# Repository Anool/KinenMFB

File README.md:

KinenMFB
========

Kinen Motherboard , Arduino based, with Raspberry-Pi interface

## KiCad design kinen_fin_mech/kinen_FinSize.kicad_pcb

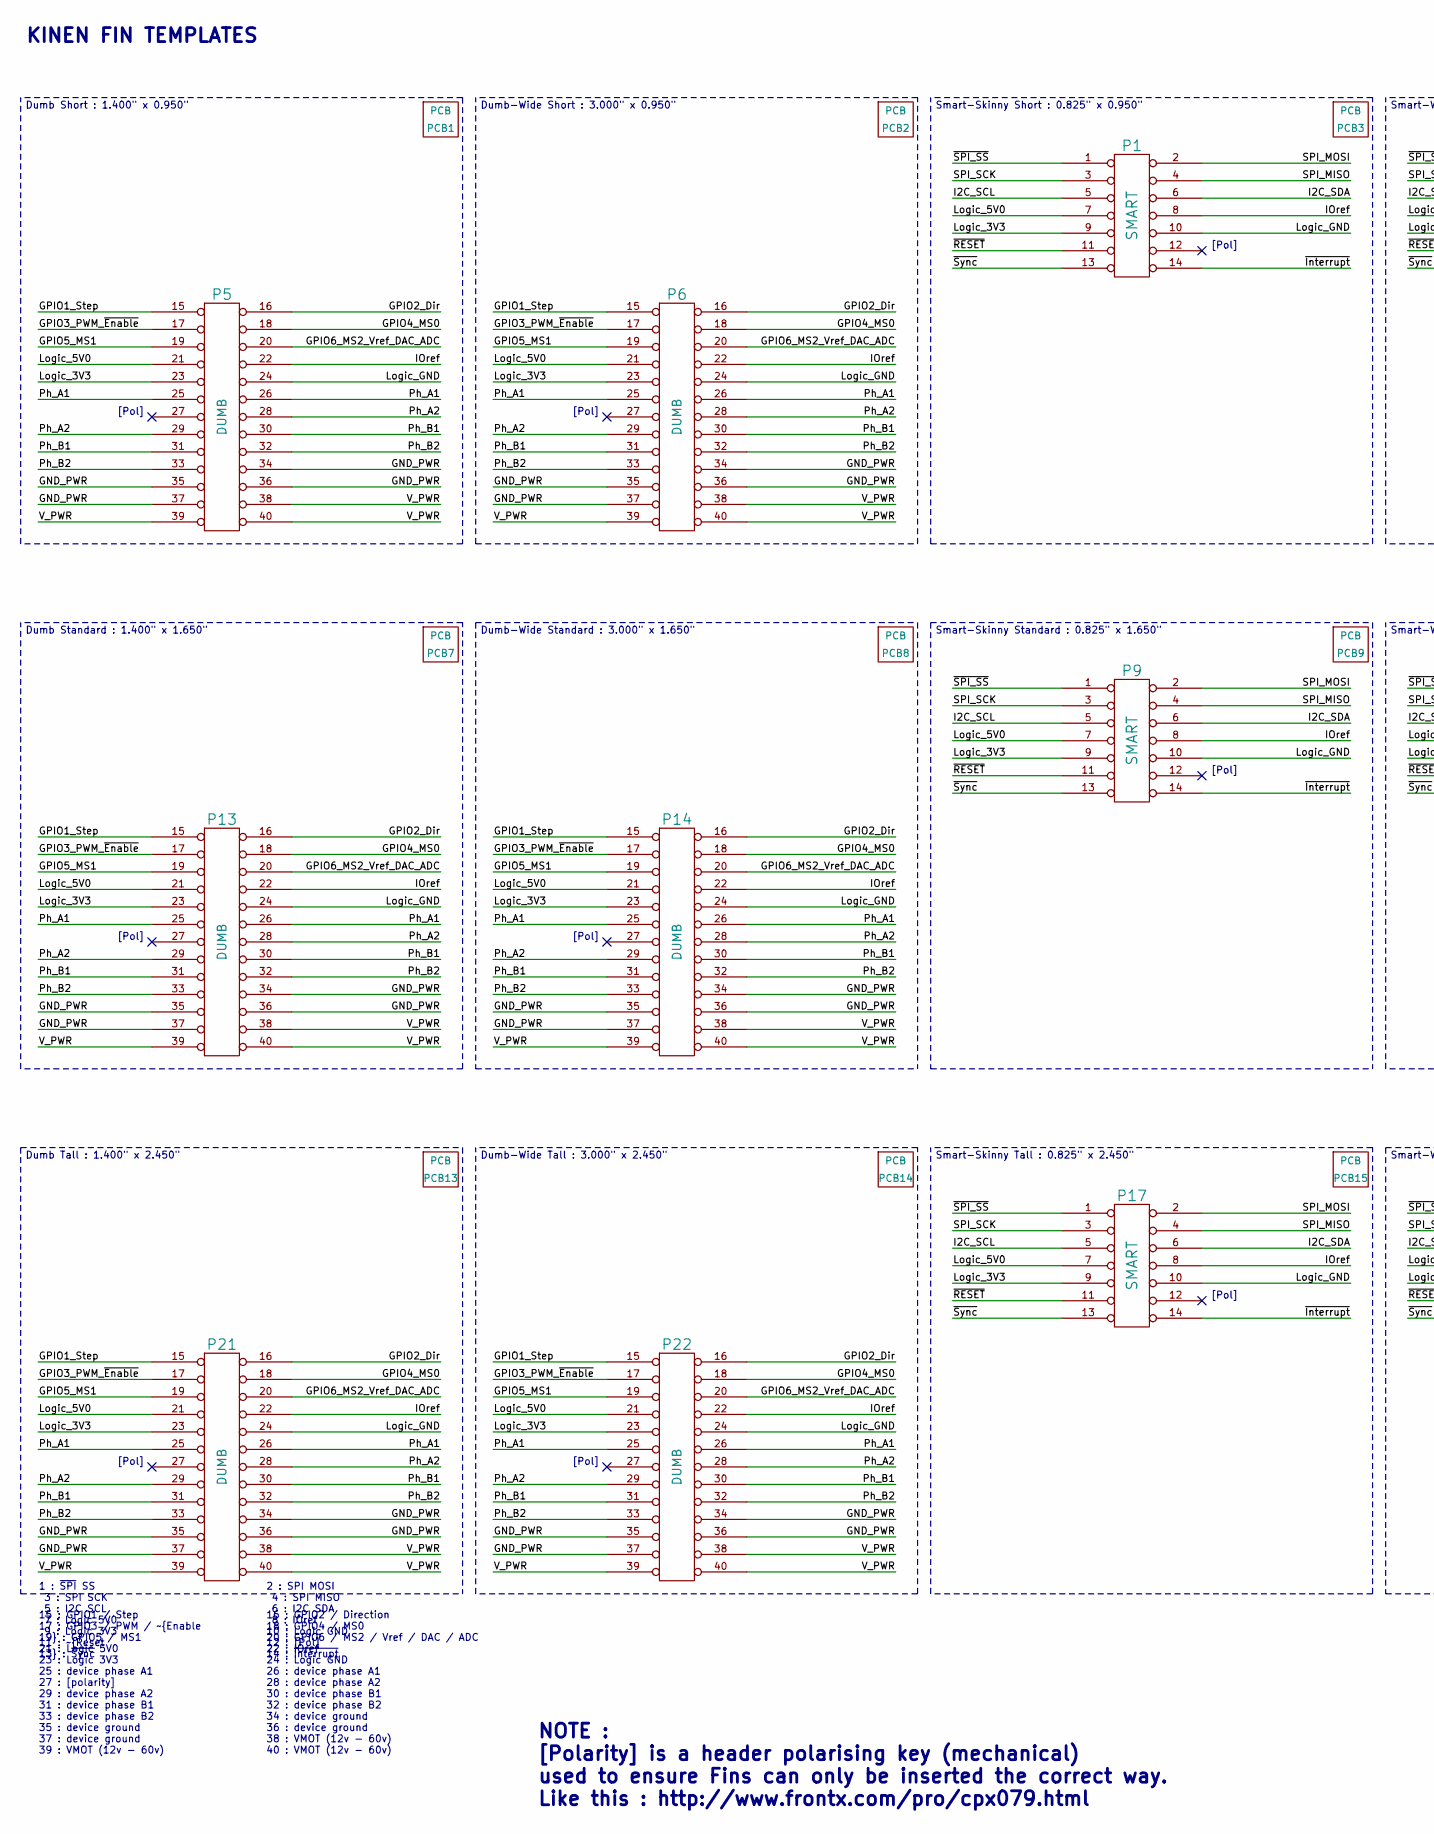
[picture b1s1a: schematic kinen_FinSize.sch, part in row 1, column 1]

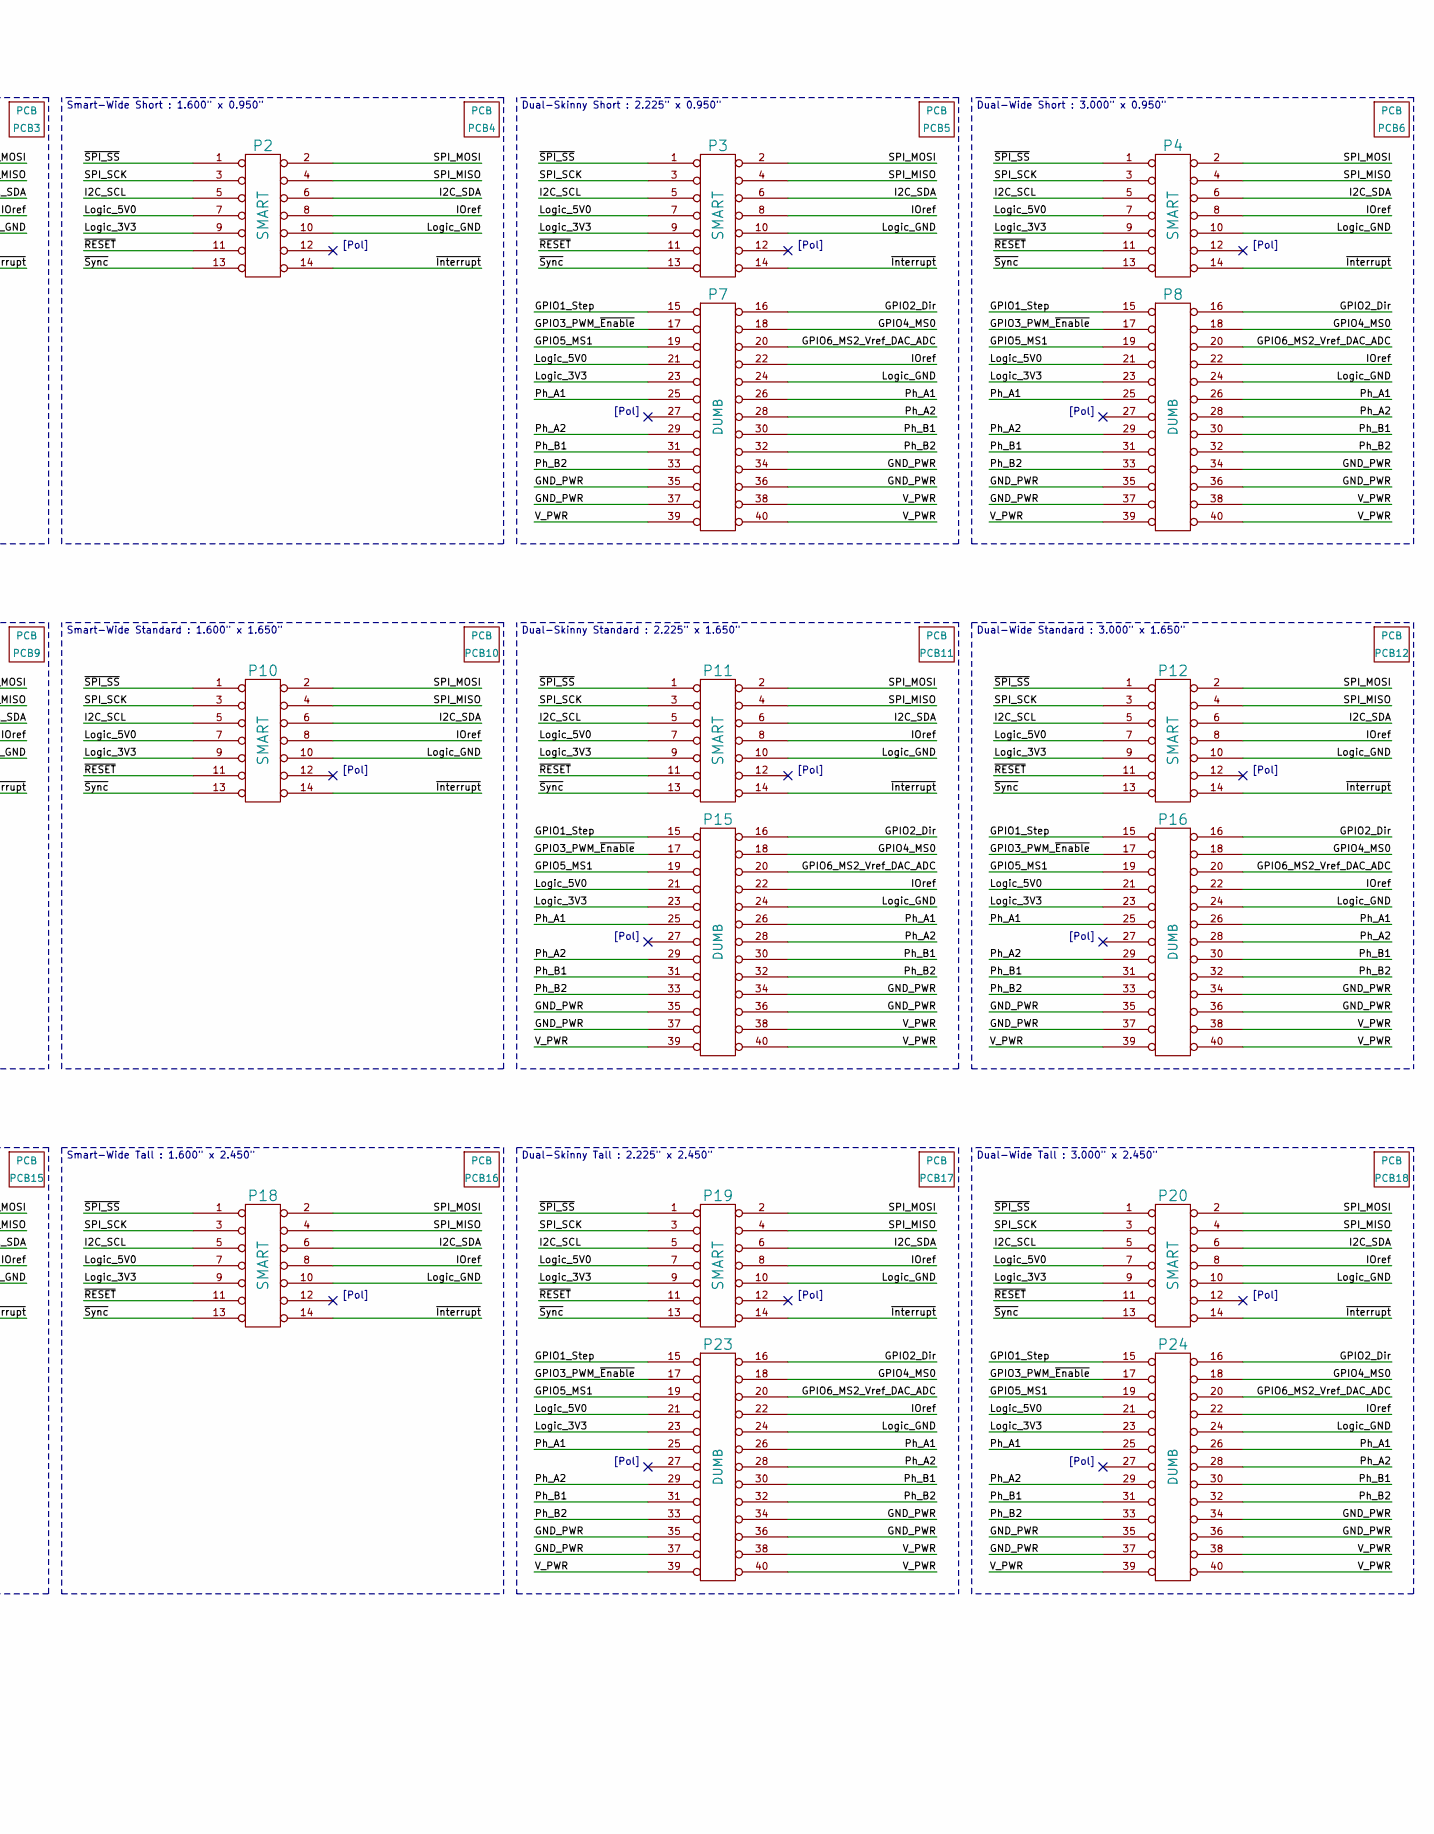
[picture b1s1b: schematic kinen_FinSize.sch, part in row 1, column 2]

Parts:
P1, P2, P3, P4, P9, P10, P11, P12, P17, P18, P19, P20: SMART; PinArray7x2/90
P5, P6, P7, P8, P13, P14, P15, P16, P21, P22, P23, P24: DUMB; PinArray13x2/90
PCB1, PCB2, PCB3, PCB4, PCB5, PCB6, PCB7, PCB8, PCB9, PCB10, PCB11, PCB12, PCB13, PCB14, PCB15, PCB16, PCB17, PCB18: PCB

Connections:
/GND_PWR: P5.34 (P20), P5.35 (P21), P5.36 (P22), P5.37 (P23), P6.34 (P20), P6.35 (P21), P6.36 (P22), P6.37 (P23), P7.34 (P20), P7.35 (P21), P7.36 (P22), P7.37 (P23), P8.34 (P20), P8.35 (P21), P8.36 (P22), P8.37 (P23), P13.34 (P20), P13.35 (P21), P13.36 (P22), P13.37 (P23), P14.34 (P20), P14.35 (P21), P14.36 (P22), P14.37 (P23), P15.34 (P20), P15.35 (P21), P15.36 (P22), P15.37 (P23), P16.34 (P20), P16.35 (P21), P16.36 (P22), P16.37 (P23), P21.34 (P20), P21.35 (P21), P21.36 (P22), P21.37 (P23), P22.34 (P20), P22.35 (P21), P22.36 (P22), P22.37 (P23), P23.34 (P20), P23.35 (P21), P23.36 (P22), P23.37 (P23), P24.34 (P20), P24.35 (P21), P24.36 (P22), P24.37 (P23)
/GPIO1_Step: P5.15 (P1), P6.15 (P1), P7.15 (P1), P8.15 (P1), P13.15 (P1), P14.15 (P1), P15.15 (P1), P16.15 (P1), P21.15 (P1), P22.15 (P1), P23.15 (P1), P24.15 (P1)
/GPIO2_Dir: P5.16 (P2), P6.16 (P2), P7.16 (P2), P8.16 (P2), P13.16 (P2), P14.16 (P2), P15.16 (P2), P16.16 (P2), P21.16 (P2), P22.16 (P2), P23.16 (P2), P24.16 (P2)
/GPIO3_PWM_~Enable: P5.17 (P3), P6.17 (P3), P7.17 (P3), P8.17 (P3), P13.17 (P3), P14.17 (P3), P15.17 (P3), P16.17 (P3), P21.17 (P3), P22.17 (P3), P23.17 (P3), P24.17 (P3)
/GPIO4_MS0: P5.18 (P4), P6.18 (P4), P7.18 (P4), P8.18 (P4), P13.18 (P4), P14.18 (P4), P15.18 (P4), P16.18 (P4), P21.18 (P4), P22.18 (P4), P23.18 (P4), P24.18 (P4)
/GPIO5_MS1: P5.19 (P5), P6.19 (P5), P7.19 (P5), P8.19 (P5), P13.19 (P5), P14.19 (P5), P15.19 (P5), P16.19 (P5), P21.19 (P5), P22.19 (P5), P23.19 (P5), P24.19 (P5)
/GPIO6_MS2_Vref_DAC_ADC: P5.20 (P6), P6.20 (P6), P7.20 (P6), P8.20 (P6), P13.20 (P6), P14.20 (P6), P15.20 (P6), P16.20 (P6), P21.20 (P6), P22.20 (P6), P23.20 (P6), P24.20 (P6)
/I2C_SCL: P1.5, P2.5, P3.5, P4.5, P9.5, P10.5, P11.5, P12.5, P17.5, P18.5, P19.5, P20.5
/I2C_SDA: P1.6, P2.6, P3.6, P4.6, P9.6, P10.6, P11.6, P12.6, P17.6, P18.6, P19.6, P20.6
/IOref: P1.8, P2.8, P3.8, P4.8, P5.22 (P8), P6.22 (P8), P7.22 (P8), P8.22 (P8), P9.8, P10.8, P11.8, P12.8, P13.22 (P8), P14.22 (P8), P15.22 (P8), P16.22 (P8), P17.8, P18.8, P19.8, P20.8, P21.22 (P8), P22.22 (P8), P23.22 (P8), P24.22 (P8)
/Logic_3V3: P1.9, P2.9, P3.9, P4.9, P5.23 (P9), P6.23 (P9), P7.23 (P9), P8.23 (P9), P9.9, P10.9, P11.9, P12.9, P13.23 (P9), P14.23 (P9), P15.23 (P9), P16.23 (P9), P17.9, P18.9, P19.9, P20.9, P21.23 (P9), P22.23 (P9), P23.23 (P9), P24.23 (P9)
/Logic_5V0: P1.7, P2.7, P3.7, P4.7, P5.21 (P7), P6.21 (P7), P7.21 (P7), P8.21 (P7), P9.7, P10.7, P11.7, P12.7, P13.21 (P7), P14.21 (P7), P15.21 (P7), P16.21 (P7), P17.7, P18.7, P19.7, P20.7, P21.21 (P7), P22.21 (P7), P23.21 (P7), P24.21 (P7)
/Logic_GND: P1.10, P2.10, P3.10, P4.10, P5.24 (P10), P6.24 (P10), P7.24 (P10), P8.24 (P10), P9.10, P10.10, P11.10, P12.10, P13.24 (P10), P14.24 (P10), P15.24 (P10), P16.24 (P10), P17.10, P18.10, P19.10, P20.10, P21.24 (P10), P22.24 (P10), P23.24 (P10), P24.24 (P10)
/Ph_A1: P5.25 (P11), P5.26 (P12), P6.25 (P11), P6.26 (P12), P7.25 (P11), P7.26 (P12), P8.25 (P11), P8.26 (P12), P13.25 (P11), P13.26 (P12), P14.25 (P11), P14.26 (P12), P15.25 (P11), P15.26 (P12), P16.25 (P11), P16.26 (P12), P21.25 (P11), P21.26 (P12), P22.25 (P11), P22.26 (P12), P23.25 (P11), P23.26 (P12), P24.25 (P11), P24.26 (P12)
/Ph_A2: P5.28 (P14), P5.29 (P15), P6.28 (P14), P6.29 (P15), P7.28 (P14), P7.29 (P15), P8.28 (P14), P8.29 (P15), P13.28 (P14), P13.29 (P15), P14.28 (P14), P14.29 (P15), P15.28 (P14), P15.29 (P15), P16.28 (P14), P16.29 (P15), P21.28 (P14), P21.29 (P15), P22.28 (P14), P22.29 (P15), P23.28 (P14), P23.29 (P15), P24.28 (P14), P24.29 (P15)
/Ph_B1: P5.30 (P16), P5.31 (P17), P6.30 (P16), P6.31 (P17), P7.30 (P16), P7.31 (P17), P8.30 (P16), P8.31 (P17), P13.30 (P16), P13.31 (P17), P14.30 (P16), P14.31 (P17), P15.30 (P16), P15.31 (P17), P16.30 (P16), P16.31 (P17), P21.30 (P16), P21.31 (P17), P22.30 (P16), P22.31 (P17), P23.30 (P16), P23.31 (P17), P24.30 (P16), P24.31 (P17)
/Ph_B2: P5.32 (P18), P5.33 (P19), P6.32 (P18), P6.33 (P19), P7.32 (P18), P7.33 (P19), P8.32 (P18), P8.33 (P19), P13.32 (P18), P13.33 (P19), P14.32 (P18), P14.33 (P19), P15.32 (P18), P15.33 (P19), P16.32 (P18), P16.33 (P19), P21.32 (P18), P21.33 (P19), P22.32 (P18), P22.33 (P19), P23.32 (P18), P23.33 (P19), P24.32 (P18), P24.33 (P19)
/SPI_MISO: P1.4, P2.4, P3.4, P4.4, P9.4, P10.4, P11.4, P12.4, P17.4, P18.4, P19.4, P20.4
/SPI_MOSI: P1.2, P2.2, P3.2, P4.2, P9.2, P10.2, P11.2, P12.2, P17.2, P18.2, P19.2, P20.2
/SPI_SCK: P1.3, P2.3, P3.3, P4.3, P9.3, P10.3, P11.3, P12.3, P17.3, P18.3, P19.3, P20.3
/V_PWR: P5.38 (P20), P5.39 (P24), P5.40 (P22), P6.38 (P20), P6.39 (P24), P6.40 (P22), P7.38 (P20), P7.39 (P24), P7.40 (P22), P8.38 (P20), P8.39 (P24), P8.40 (P22), P13.38 (P20), P13.39 (P24), P13.40 (P22), P14.38 (P20), P14.39 (P24), P14.40 (P22), P15.38 (P20), P15.39 (P24), P15.40 (P22), P16.38 (P20), P16.39 (P24), P16.40 (P22), P21.38 (P20), P21.39 (P24), P21.40 (P22), P22.38 (P20), P22.39 (P24), P22.40 (P22), P23.38 (P20), P23.39 (P24), P23.40 (P22), P24.38 (P20), P24.39 (P24), P24.40 (P22)
/~Interrupt: P1.14, P2.14, P3.14, P4.14, P9.14, P10.14, P11.14, P12.14, P17.14, P18.14, P19.14, P20.14
/~RESET: P1.11, P2.11, P3.11, P4.11, P9.11, P10.11, P11.11, P12.11, P17.11, P18.11, P19.11, P20.11
/~SPI_SS: P1.1, P2.1, P3.1, P4.1, P9.1, P10.1, P11.1, P12.1, P17.1, P18.1, P19.1, P20.1
/~Sync: P1.13, P2.13, P3.13, P4.13, P9.13, P10.13, P11.13, P12.13, P17.13, P18.13, P19.13, P20.13

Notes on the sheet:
15 : GPIO1 / Step 17 : GPIO3 / PWM / ~Enable 19 : GPIO5 / MS1 21 : Logic 5V0 23 : Logic 3V3 25 : device phase A1 27 : [polarity] 29 : device phase A2 31 : device phase B1 33 : device phase B2 35 : device ground 37 : device ground 39 : VMOT (12v - 60v)
16 : GPIO2 / Direction 18 : GPIO4 / MS0 20 : GPIO6 / MS2 / Vref / DAC / ADC 22 : IOref 24 : Logic GND 26 : device phase A1 28 : device phase A2 30 : device phase B1 32 : device phase B2 34 : device ground 36 : device ground 38 : VMOT (12v - 60v) 40 : VMOT (12v - 60v)
NOTE : [Polarity] is a header polarising key (mechanical) used to ensure Fins can only be inserted the correct way. Like this : http://www.frontx.com/pro/cpx079.html
1 : ~SPI SS 3 : SPI SCK 5 : I2C SCL 7 : Logic 5V0 9 : Logic 3V3 11 : ~Reset 13 : ~Sync
2 : SPI MOSI 4 : SPI MISO 6 : I2C SDA 8 : IOref 10 : Logic GND 12 : [Pol] 14 : ~Interrupt
[Pol]
KINEN FIN TEMPLATES
Dumb Short : 1.400" x 0.950"
Dumb-Wide Short : 3.000" x 0.950"
Smart-Wide Short : 1.600" x 0.950"
Smart-Skinny Short : 0.825" x 0.950"
Dual-Skinny Short : 2.225" x 0.950"
Dual-Wide Short : 3.000" x 0.950"
Dual-Wide Standard : 3.000" x 1.650"
Dual-Skinny Standard : 2.225" x 1.650"
Smart-Skinny Standard : 0.825" x 1.650"
Smart-Wide Standard : 1.600" x 1.650"
Dumb-Wide Standard : 3.000" x 1.650"
Dumb Standard : 1.400" x 1.650"
Dumb Tall : 1.400" x 2.450"
Dumb-Wide Tall : 3.000" x 2.450"
Smart-Wide Tall : 1.600" x 2.450"
Smart-Skinny Tall : 0.825" x 2.450"
Dual-Skinny Tall : 2.225" x 2.450"
Dual-Wide Tall : 3.000" x 2.450"

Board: 2 copper layers, 42 parts (0 on the bottom side), 25 nets, no tracks yet.

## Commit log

2013-03-01 Initial commit for KinenMFB
2013-03-01 this commit is to check if I can get GIT and SVN both to work on same directory
2013-03-07 removed old svn folder
2013-03-07 Added feature list for KinenMFB
2013-03-15 Added some Data sheets for reference. SAM3X8E, Arduino Due.
2013-03-22 Moved kinen_MB (motherboard) and kinen_fin (mech) to separate folders for a cleaner project folder. SAM3X8E schematic symbol created.
